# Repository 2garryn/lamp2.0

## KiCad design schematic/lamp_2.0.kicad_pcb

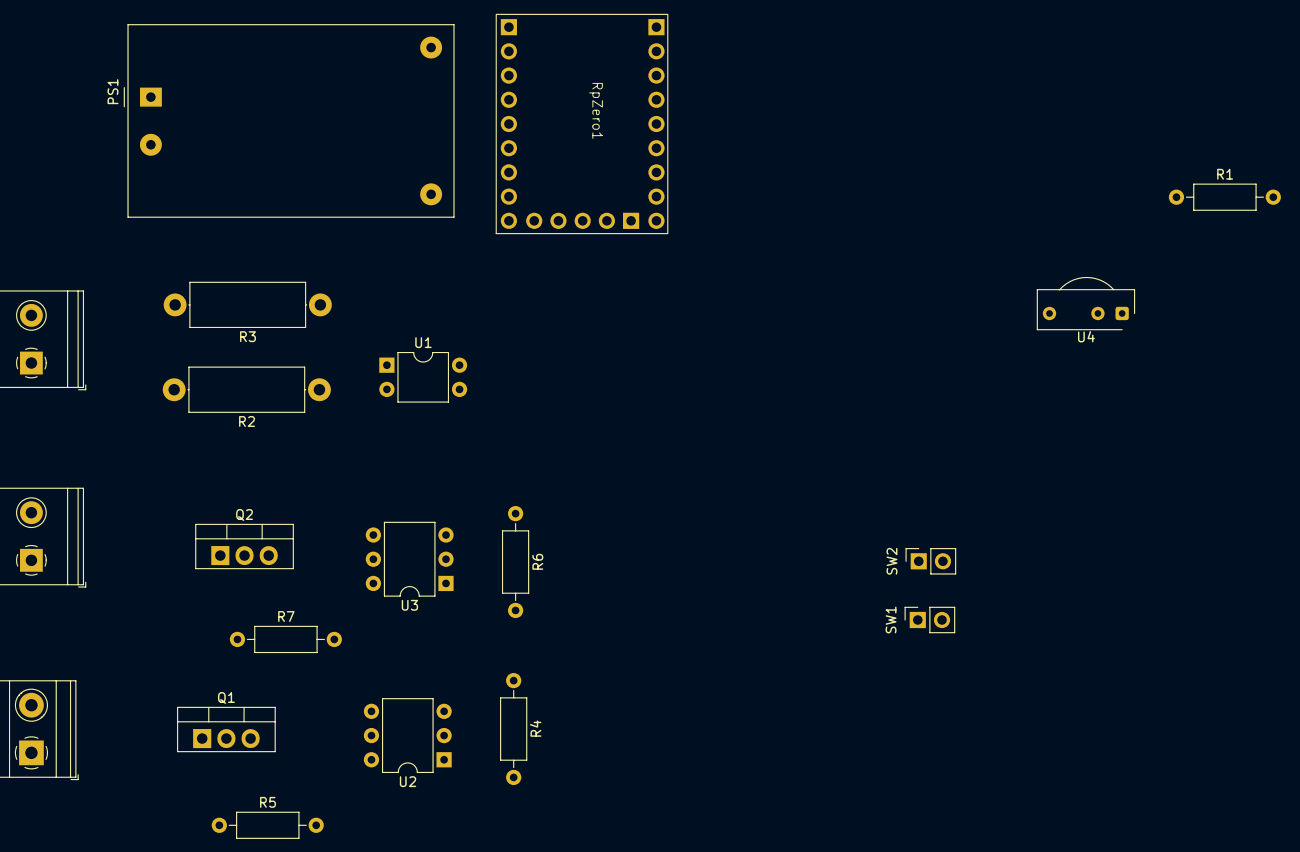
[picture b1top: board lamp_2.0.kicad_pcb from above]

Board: 2 copper layers, 20 parts (0 on the bottom side), 21 nets, no tracks yet.

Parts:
J1: 220V; TerminalBlock_Philmore_TB132_1x02_P5.00mm_Horizontal
J2: Disco lamp; TerminalBlock_Philmore_TB132_1x02_P5.00mm_Horizontal
J3: Edison lamp; TerminalBlock_Phoenix_MKDS-1,5-2_1x02_P5.00mm_Horizontal
PS1: HLK-PM01; Converter_ACDC_HiLink_HLK-PMxx
Q1, Q2: BTA16; TO-220-3_Vertical
R1: 10k; R_Axial_DIN0207_L6.3mm_D2.5mm_P10.16mm_Horizontal
R2, R3: 51k; R_Axial_DIN0414_L11.9mm_D4.5mm_P15.24mm_Horizontal
R4, R6: 220; R_Axial_DIN0207_L6.3mm_D2.5mm_P10.16mm_Horizontal
R5, R7: 1k; R_Axial_DIN0207_L6.3mm_D2.5mm_P10.16mm_Horizontal
RpZero1: RP-2040-FP
SW1: Disco; PinSocket_1x02_P2.54mm_Vertical
SW2: Edison; PinSocket_1x02_P2.54mm_Vertical
U1: EL814; DIP-4_W7.62mm
U2, U3: MOC3021; DIP-6_W7.62mm
U4: TSOP31238; Vishay_CAST-3Pin

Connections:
+3.3V: R1.2, U4.2 (Vs)
/ADC0: R1.1, RpZero1.7 (26), U1.4
/Disco pin (binary): R6.1, RpZero1.22 (1)
GND: PS1.3 (-Vout), RpZero1.2 (GND), SW1.2, SW2.2, U1.3, U2.2, U3.2, U4.1 (GND)
unnamed: J1.1, J2.2, J3.2, PS1.2 (AC/N), R2.2
unnamed: J1.2, PS1.1 (AC/L), Q1.2 (A2), Q2.2 (A2), R3.2, R5.1, R7.1
unnamed: J2.1, Q2.1 (A1)
unnamed: J3.1, Q1.1 (A1)
unnamed: PS1.4 (+Vout), RpZero1.1 (5V)
unnamed: Q1.3 (G), U2.4
unnamed: Q2.3 (G), U3.4
unnamed: R2.1, U1.2
unnamed: R3.1, U1.1
unnamed: R4.2, U2.1
unnamed: R5.2, U2.6
unnamed: R6.2, U3.1
unnamed: R7.2, U3.6
unnamed: R4.1, RpZero1.23 (0)
unnamed: RpZero1.17 (6), U4.3 (OUT)
unnamed: RpZero1.16 (7), SW1.1
unnamed: RpZero1.15 (8), SW2.1

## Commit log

2024-01-24 schematic
2024-01-25 finished schema
